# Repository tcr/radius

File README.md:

# radius

## testing

```
make
make flash
make test
```

If OS X reports contention for your device:

```
sudo kextunload -b com.apple.driver.AppleUSBCardReader
sudo kextunload -b com.apple.iokit.IOUSBMassStorageClass
```

## parts

Designator(s) | Quantity | Description | Part Number
--- | --- | --- | ---
IC1 | 1 | STM8S 8-bit micro (TSSOP-20) | [STM8S003F3P6](http://www.digikey.com/product-detail/en/STM8S003F3P6/497-11946-5-ND/2765682)
P2 | 1 | 10-pin right-angled header, .1" Pitch | [PPTC101LGBN-RC](http://www.digikey.com/product-search/en?KeyWords=S5446-ND&WT.z_header=search_go)
U1 | 1 | Full speed USB <-> 9-pin Serial (SOP-16) | CH340G
U2 | 1 | 3.3V Regulator (SO-8) | [LD1117D33CTR](http://www.digikey.com/scripts/DkSearch/dksus.dll?Detail&itemSeq=175125035&uq=635712533888642171)
Y1 | 1 | 12Mhz Crystal | [NX3225SA](http://www.digikey.com/product-detail/en/NX3225SA-12.000MHZ-STD-CSR-1/644-1047-1-ND/1128919)
C1 | 1 | 0.1 uF (0603) | ...
C2 | 1 | 10 uF (0603) | ...
C3 | 1 | 1 μF polarized (0603) | ...
C4, C5 | 2 | 20 pF (0603) | ...

* [STM8 Reference design](http://www.st.com/web/en/resource/technical/document/application_note/CD00194637.pdf#page=19)

## pin mapping

* GND
* 3.3V
* SCL - PB4
* SDA - PB5
* SCK - PC5
* MISO - PC7
* MOSI - PC6
* TXD - PD2
* RXD - PD0
* G3 - PD1

USB:

* TXD - PD6
* RXD - PD5

## docs

Reference manual: http://www.st.com/web/en/resource/technical/document/reference_manual/CD00190271.pdf

 * SPI: http://www.st.com/web/en/resource/technical/document/reference_manual/CD00190271.pdf#page=259
 * I2C: http://www.st.com/web/en/resource/technical/document/reference_manual/CD00190271.pdf#page=285
 * GPIO: http://www.st.com/web/en/resource/technical/document/reference_manual/CD00190271.pdf#page=106
 * UART: http://www.st.com/web/en/resource/technical/document/reference_manual/CD00190271.pdf#page=318

CPU reference: http://www.st.com/web/en/resource/technical/document/programming_manual/CD00161709.pdf

Product Datasheet: http://www.st.com/web/en/resource/technical/document/datasheet/DM00024550.pdf

 * Memory map: http://www.st.com/web/en/resource/technical/document/datasheet/DM00024550.pdf#page=32
 * Pin map: http://www.st.com/web/en/resource/technical/document/datasheet/DM00024550.pdf#page=22

 Errata: http://postar.sino-star.com/public/uploads/20120214161049_871.pdf

## CH340G

Datasheet: http://www.seeedstudio.com/wiki/images/7/7c/CH340DS1_EN.PDF

## tools

https://github.com/vdudouyt/stm8flash

```
brew install sdcc
```

http://www.colecovision.eu/stm8/128-EVAL%20Dhrystone.shtml

## how it works

interrupts are priority-based outputs in 64 byte packets. priority output is real time input of "uniterruptable streams", specifically i2c read (max 920Khz) and uart input (max 18400bps) simultaneously

also note that i2c can stretch clock lines so really it's only uart interrupts

there are many buffers, but this one is mine(d) for its outputting content. all packets block on new input until it's swapped for the outputting. so buffers must clean faster than they collectively are filled for uninterruptable streams (and acks).

output from radius is asap and dumped into its buffers. simple packet id +  NACK/ACK acknowledgement byte on the usb line.

ID0 + NACK/ACK
ID1 + LEN + <=64 byte packet

input? it is 64 byte packets. wait for an nack, then resend, or continue

LEN + <=64 byte packet

input is synced at start by waiting for an 'R' on both sides

packets are USB-style repeated until a 0 length packet or < 64 length packet is received

## license

MIT/ASL2

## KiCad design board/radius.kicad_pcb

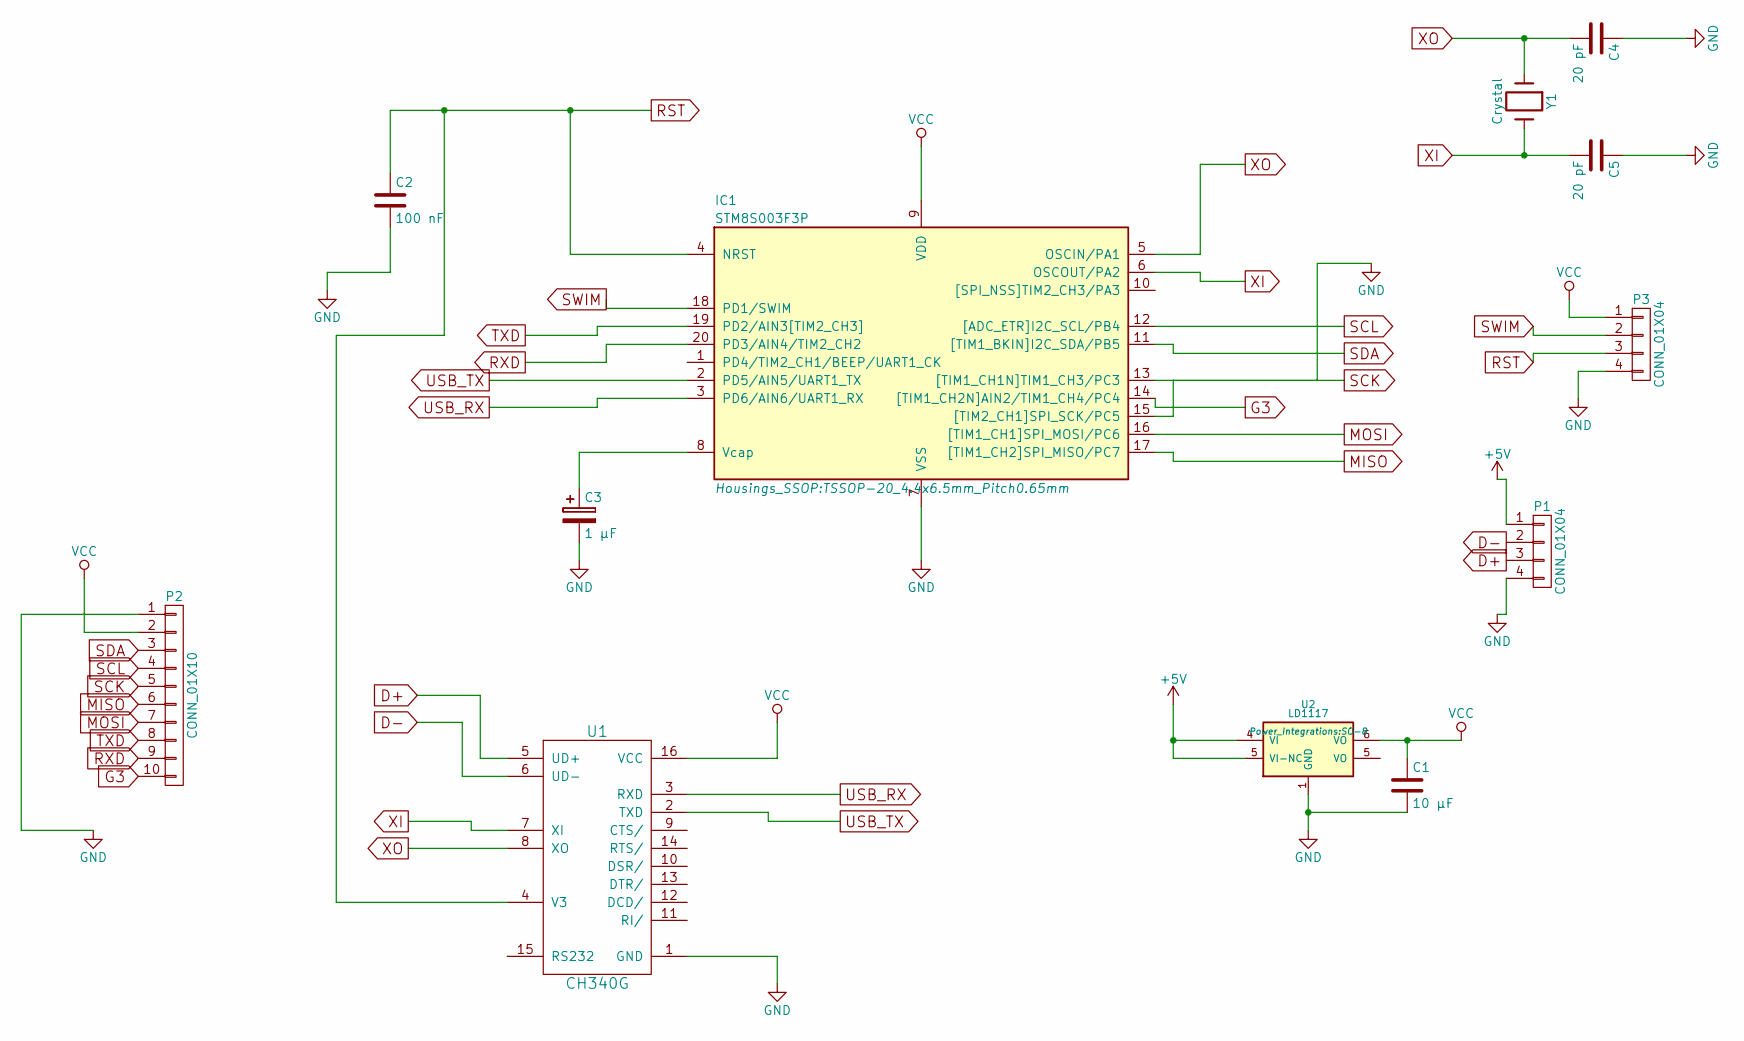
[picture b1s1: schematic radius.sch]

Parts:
C1: 10 µF; C_0603_HandSoldering
C2: 100 nF; C_0603_HandSoldering
C3: 1 μF; C_0603_HandSoldering
C4, C5: 20 pF; C_0603_HandSoldering
IC1: STM8S003F3P; TSSOP-20_4.4x6.5mm_Pitch0.65mm
P1: CONN_01X04; USB-A-PCB
P2: CONN_01X10; Socket_Strip_Angled_1x10
P3: CONN_01X04; RADIUS-CONN-2MM-M-1x4
U1: CH340G; SO-16-N
U2: LD1117; SO-8
Y1: Crystal; Crystal_SMD_0603_4Pads

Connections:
+5V: P1.1, U2.4 (VI), U2.5 (VI-NC)
D+: P1.3, U1.5 (UD+)
D-: P1.2, U1.6 (UD-)
G3: IC1.14 ([TIM1_CH2N]AIN2/TIM1_CH4/PC4), P2.10
GND: C1.2, C2.2, C3.2, C4.1, C5.1, IC1.7 (VSS), IC1.13 ([TIM1_CH1N]TIM1_CH3/PC3), P1.4, P2.1, P3.4, U1.1 (GND), U2.1 (GND)
MISO: IC1.17 ([TIM1_CH2]SPI_MISO/PC7), P2.6
MOSI: IC1.16 ([TIM1_CH1]SPI_MOSI/PC6), P2.7
unnamed: C3.1, IC1.8 (Vcap)
RST: C2.1, IC1.4 (NRST), P3.3, U1.4 (V3)
RXD: IC1.20 (PD3/AIN4/TIM2_CH2), P2.9
SCK: IC1.15 ([TIM2_CH1]SPI_SCK/PC5), P2.5
SCL: IC1.12 ([ADC_ETR]I2C_SCL/PB4), P2.4
SDA: IC1.11 ([TIM1_BKIN]I2C_SDA/PB5), P2.3
SWIM: IC1.18 (PD1/SWIM), P3.2
TXD: IC1.19 (PD2/AIN3[TIM2_CH3]), P2.8
USB_RX: IC1.3 (PD6/AIN6/UART1_RX), U1.3 (RXD)
USB_TX: IC1.2 (PD5/AIN5/UART1_TX), U1.2 (TXD)
VCC: C1.1, IC1.9 (VDD), P2.2, P3.1, U1.16 (VCC), U2.6 (VO)
XI: C5.2, IC1.6 (OSCOUT/PA2), U1.7 (XI), Y1.2
XO: C4.2, IC1.5 (OSCIN/PA1), U1.8 (XO), Y1.1

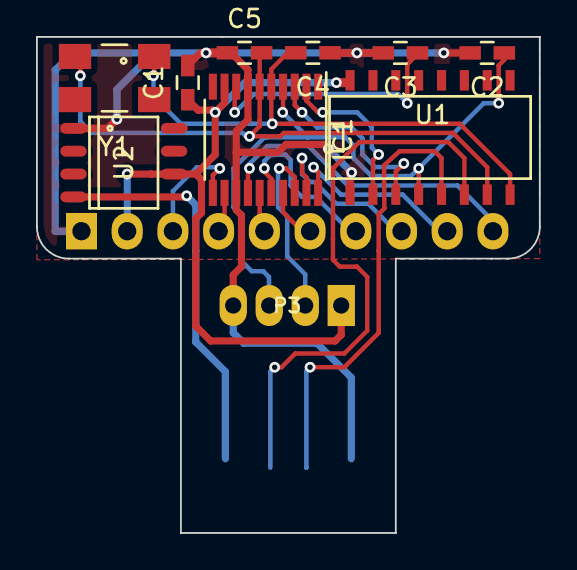
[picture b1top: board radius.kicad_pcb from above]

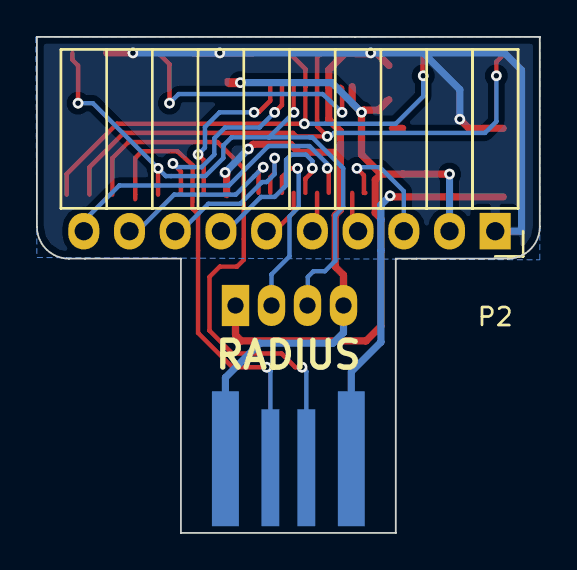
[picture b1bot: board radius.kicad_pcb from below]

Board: 2 copper layers, 27.9 x 27.6 mm, 12 parts (2 on the bottom side), 20 nets.

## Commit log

2015-05-01 Initial commit of STM8 code.
2015-05-02 Adds README
2015-05-02 Exclude etc/ dir
2015-05-02 Adds documentation.
2015-05-03 Blinky
2015-05-05 Supports timers.
2015-05-05 Adds UART output.
2015-05-05 Removes old portme file.
2015-05-06 Supports echo over UART.
2015-05-22 Supports a "make test" function.
2015-05-22 Adds port argument to test script.
2015-05-22 Adds pin mapping.
2015-05-22 Changes.
2015-05-23 Successfully reads accelerometer ID.
2015-05-23 Allows main loop to run.
2015-05-23 Interrupt-based I2C transmission.
2015-05-23 Cleans up code.
2015-05-23 Corrects UART interrupts to handle Rx.
2015-05-23 Corrects test to work with I2C.
2015-05-26 Supports reading of custom registers.
2015-05-26 Switches to using a value buffer.
2015-05-26 Fixes multibyte I2C transfer.
2015-05-26 Supports multibyte I2C read.
2015-05-26 Adds response marker.
2015-05-29 Adds make target to unload drivers.
2015-05-29 Cleans up code in main.c
2015-05-29 Ups baud to 57600.
2015-06-01 Adds CH340G datasheet.
2015-06-16 Adds initial schematic files.
2015-06-18 Commit #2
2015-06-18 New change
2015-06-18 Cleans up upper components.
2015-06-18 Qualifying layout
2015-06-21 Redone
2015-06-24 Tighest layout
2015-06-25 Adds missing capacitor on regulator.
2015-06-26 Adds USB connector.
2015-06-26 Expands footprint of board.
2015-06-28 Corrects footprints for CH340G, start over.
2015-06-29 Thicker traces.
2015-06-29 New alignment.
2015-06-29 Board edges.
2015-06-29 Completed edges.
2015-06-29 Completes power rails, layout.
2015-06-29 Arcs!
2015-06-29 Polish.
2015-06-29 Text.
2015-06-30 Updates paths for files. adds renders, gerbers.
2015-06-30 Undoes main.c and test patches.
2015-06-30 Removes old footprints.
2015-06-30 Adds Radius renders.
2015-06-30 Moves source files to src/
2015-06-30 Adds parts.
2015-06-30 Updates Capacitor values.
2015-07-20 Widens board to 1.1"
2015-07-20 Support SWIM connector.
2015-07-20 Corrects power adapter pinout.
2015-07-20 Adds README documentation.
2015-07-20 Flips RADIUS text side.
2015-07-21 Fixes paths.
2015-07-21 Fixes makefile paths.
2015-07-21 Adds interrupt documentation.
2015-07-21 Updates schematic traces and RADIUS text.
